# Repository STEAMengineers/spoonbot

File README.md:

# spoonbot
Spoonbot is a social energy indicator robot pcb based on a CH32v003J4M6 microcontroller, using a thumbwheel potentiometer to light some or all of the 5 leds.  It was designed for a smd soldering workshop we ran with MCQN at DoES Livepool.

This repo contains the code for the microcontroller and a kicad version of the pcb design. Because we used JLC colour silkscreen for our badges the hardware folder is an export from EasyEDA. It is highly recommended that you run DRC on the pcb before exporting for production.

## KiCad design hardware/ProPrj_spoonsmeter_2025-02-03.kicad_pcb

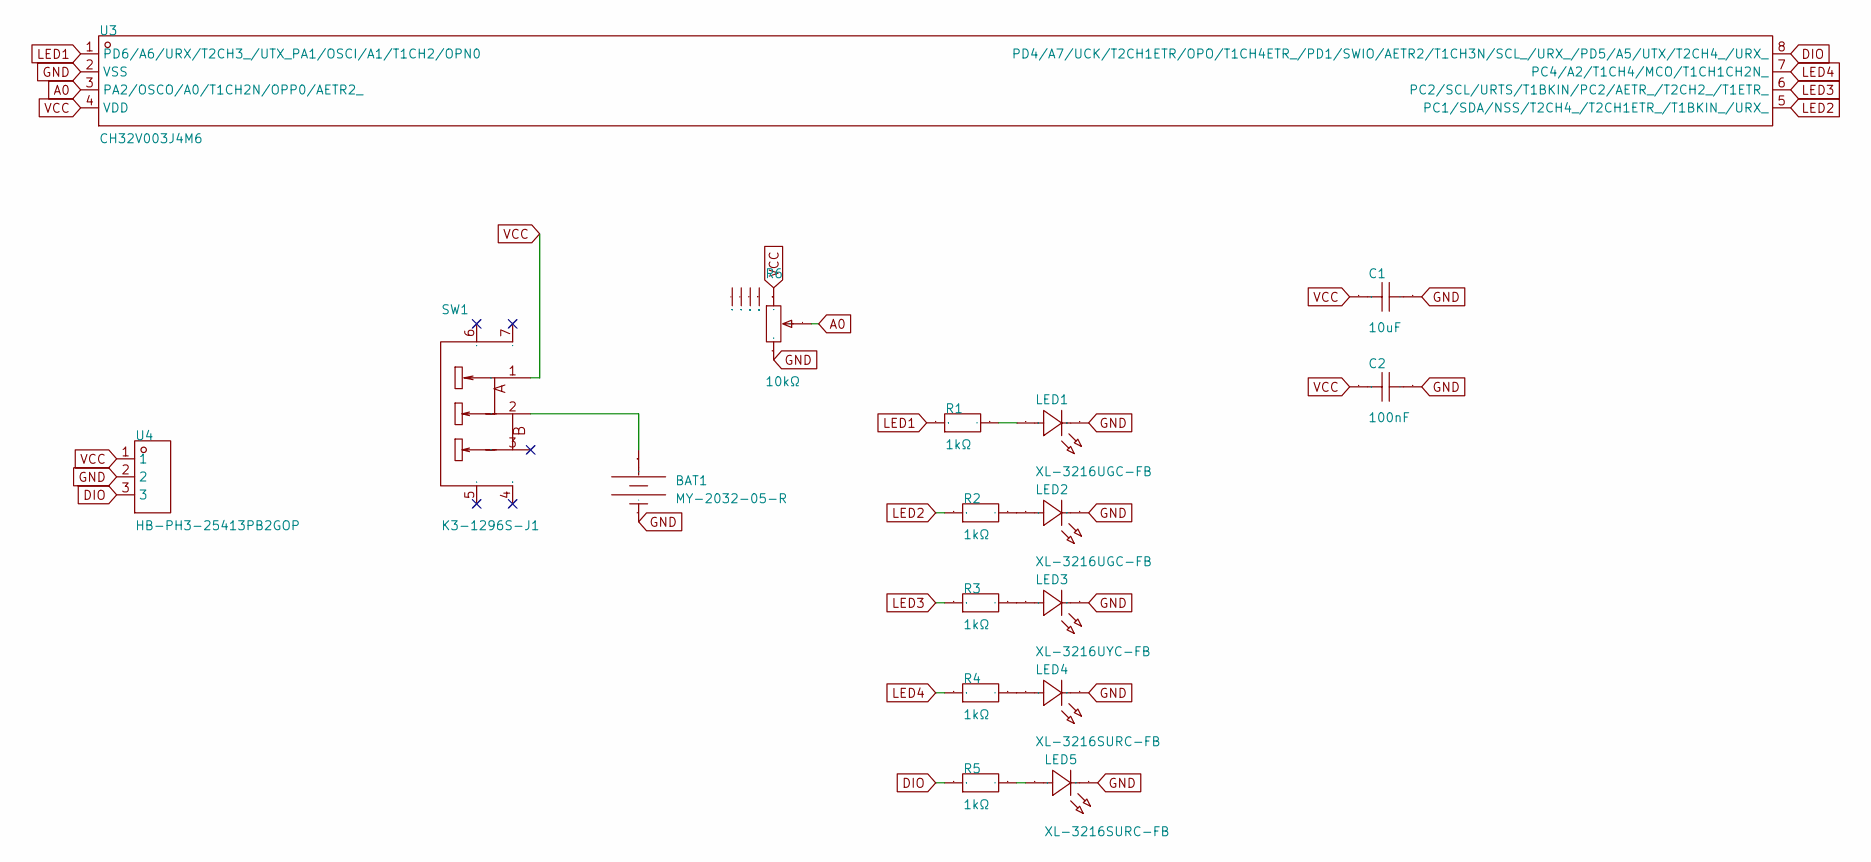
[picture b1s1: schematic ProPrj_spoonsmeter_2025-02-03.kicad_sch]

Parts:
BAT1: MY-2032-05-R; BAT-SMD_MY-2032-05-R; Manufacturer Part MY-2032-05-R; LCSC Part Name 电池扣 适用电池:CR2032
C1: 10uF; C0805; Manufacturer Part C0805X106K010T; LCSC Part Name 10uF ±10% 10V
C2: 100nF; C0805; Manufacturer Part C0805X104K251T; LCSC Part Name 100nF ±10% 250V
LED1, LED2: XL-3216UGC-FB; LED1206-RD_RED_LTST-C230CKT; Manufacturer Part XL-3216UGC-FB; LCSC Part Name XL-3216UGC-FB
LED3: XL-3216UYC-FB; LED1206-RD_RED_LTST-C230CKT; Manufacturer Part XL-3216UYC-FB; LCSC Part Name XL-3216UYC-FB
LED4, LED5: XL-3216SURC-FB; LED1206-RD_RED_LTST-C230CKT; Manufacturer Part XL-3216SURC-FB; LCSC Part Name XL-3216SURC-FB
R1, R2, R3, R4, R5: 1kΩ; R0805; Manufacturer Part SCR0805J1K; LCSC Part Name 厚膜电阻 1kΩ ±5% 125mW
R6: 10kΩ; RES-SMD_RK10J11R0A0H; Manufacturer Part RK10J11R0A0H; LCSC Part Name 10kΩ ±30%
SW1: K3-1296S-J1; SW-SMD_K3-1296S-J1; Manufacturer Part K3-1296S-J1; LCSC Part Name 柄长2.3mm卧贴双档 滑动开关
U3: CH32V003J4M6; SOP-8_L4.9-W3.8-P1.27-LS6.0-BL; Manufacturer Part CH32V003J4M6; LCSC Part Name CH32V003J4M6
U4: HB-PH3-25413PB2GOP; HDR-TH_3P-P2.54-V-M; Manufacturer Part HB-PH3-25413PB2GOP; LCSC Part Name 间距:2.54mm 1x3P 直插 方针

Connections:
$1N1644: BAT1.1 (+), SW1.2
$1N2487: LED3.2 (A), R3.2
$1N2528: LED2.2 (A), R2.2
$1N2533: LED4.2 (A), R4.2
$1N2535: LED1.2 (A), R1.2
$1N2553: LED5.2 (A), R5.2
A0: R6.2, U3.3 (PA2/OSCO/A0/T1CH2N/OPP0/AETR2_)
DIO: R5.1, U3.8 (PD4/A7/UCK/T2CH1ETR/OPO/T1CH4ETR_/PD1/S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), U4.3
GND: BAT1.2 (-), C1.2, C2.2, LED1.1 (K), LED2.1 (K), LED3.1 (K), LED4.1 (K), LED5.1 (K), R6.3, U3.2 (VSS), U4.2
LED1: R1.1, U3.1 (PD6/A6/URX/T2CH3_/UTX_PA1/OSCI/A1/T1CH2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)
LED2: R2.1, U3.5 (PC1/SDA/NSS/T2CH4_/T2CH1ETR_/T1BKIN_/UR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)
LED3: R3.1, U3.6 (PC2/SCL/URTS/T1BKIN/PC2/AETR_/T2CH2_/T1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)
LED4: R4.1, U3.7 (PC4/A2/T1CH4/MCO/T1CH1CH2N_)
VCC: C1.1, C2.1, R6.1, SW1.1, U3.4 (VDD), U4.1

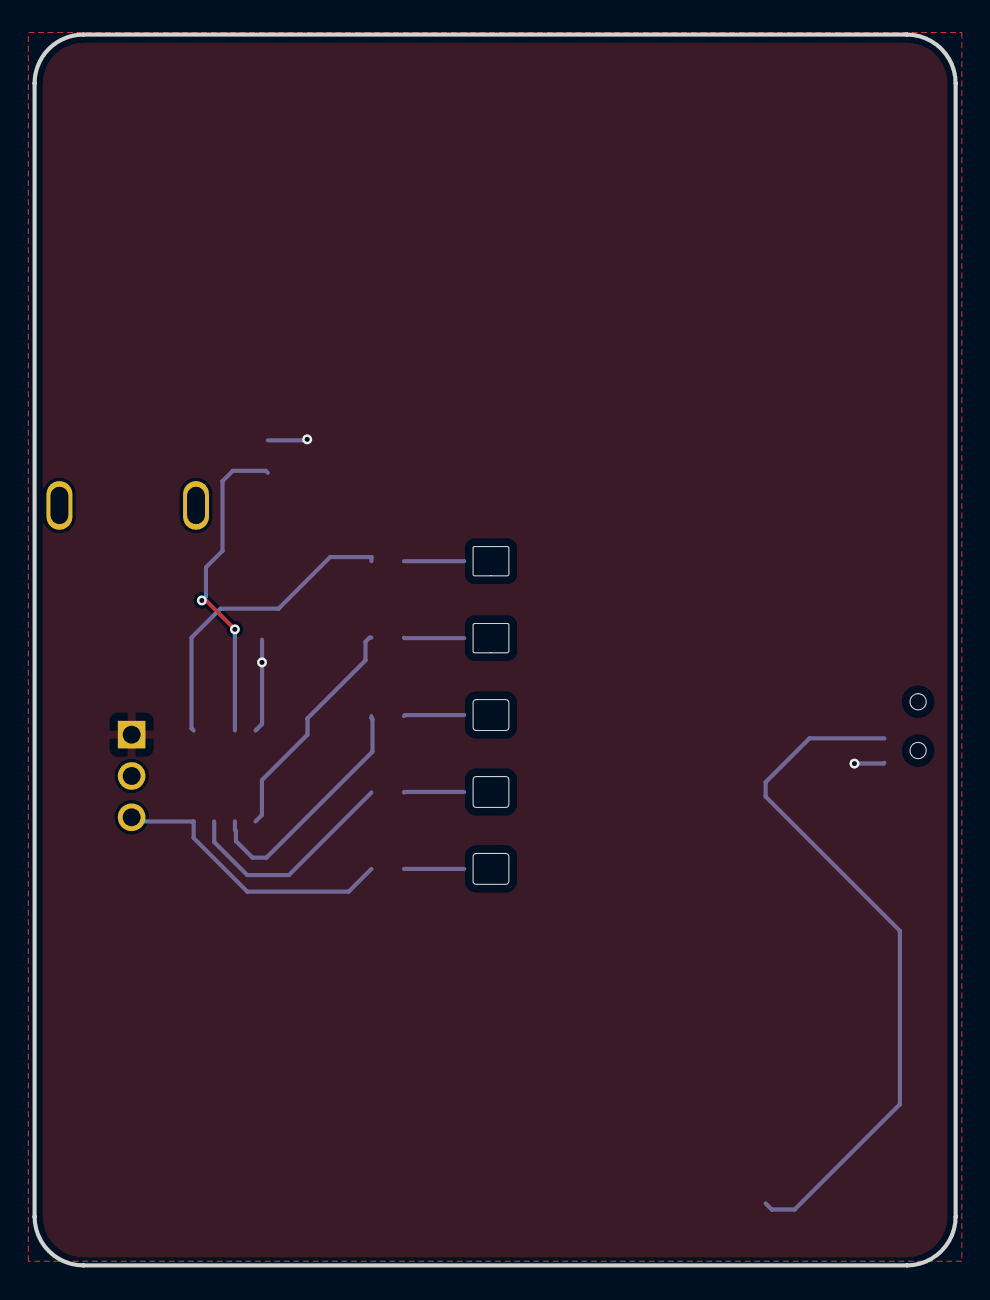
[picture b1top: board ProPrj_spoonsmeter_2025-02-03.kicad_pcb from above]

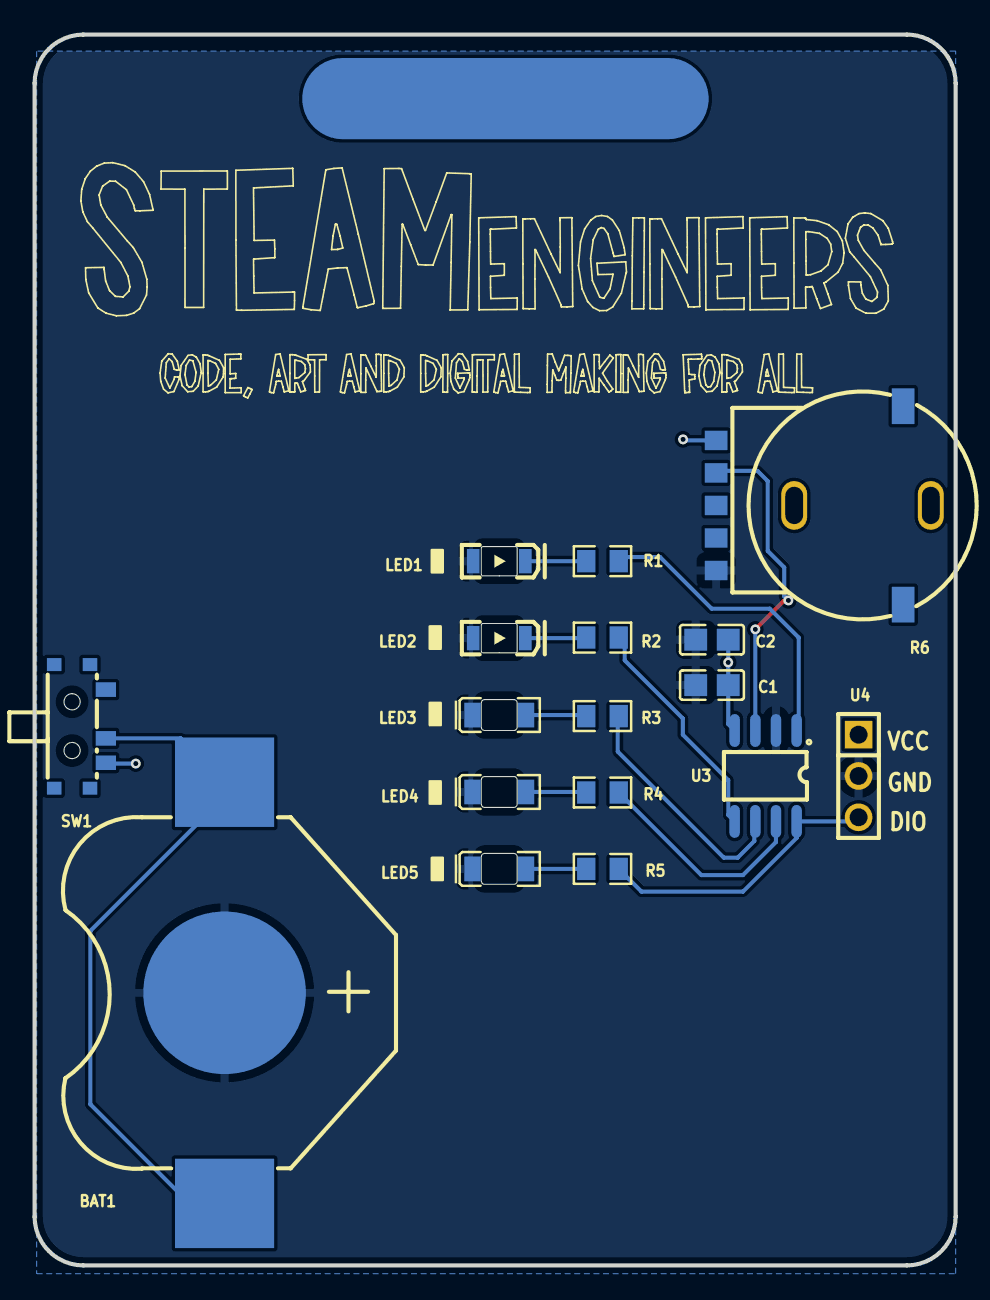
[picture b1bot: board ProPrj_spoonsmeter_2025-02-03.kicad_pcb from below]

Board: 2 copper layers, 56.6 x 75.7 mm, 17 parts (17 on the bottom side), 14 nets.

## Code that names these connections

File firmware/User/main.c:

/********************************** (C) COPYRIGHT *******************************
 * File Name          : main.c
 * Author             : WCH
 * Version            : V1.0.0
 * Date               : 2023/12/25
 * Description        : Main program body.
 *********************************************************************************
 * Copyright (c) 2021 Nanjing Qinheng Microelectronics Co., Ltd.
 * Attention: This software (modified or not) and binary are used for 
 * microcontroller manufactured by Nanjing Qinheng Microelectronics.
 *******************************************************************************/

/*
 *@Note
 *Multiprocessor communication mode routine:
 *Master:USART1_Tx(PD5)\USART1_Rx(PD6).
 *This routine demonstrates that USART1 receives the data sent by CH341 and inverts
 *it and sends it (baud rate 115200).
 *
 *Hardware connection:PD5 -- Rx
 *                     PD6 -- Tx
 *
 */

#include "debug.h"


/* Global define */


/* Global Variable */
vu8 val;

/*********************************************************************
 * @fn      init_gpio
 *
 * @brief   Initializes PC1,2 & 4 and PA1.
 *
 * @return  none
 */
void init_gpio(void)
{
    ADC_InitTypeDef ADC_InitStructure = {0};
    GPIO_InitTypeDef  GPIO_InitStructure = {0};

    RCC_APB2PeriphClockCmd(RCC_APB2Periph_GPIOC | RCC_APB2Periph_GPIOA | RCC_APB2Periph_GPIOD, ENABLE);

    /* Port C1=led2 2=led3 4=led4 */
    GPIO_InitStructure.GPIO_Pin = GPIO_Pin_1 | GPIO_Pin_2 | GPIO_Pin_4;
    GPIO_InitStructure.GPIO_Speed = GPIO_Speed_30MHz;
    GPIO_InitStructure.GPIO_Mode = GPIO_Mode_Out_PP;
    GPIO_Init(GPIOC, &GPIO_InitStructure);

    /* Port D6=led1 D4=led5*/
    GPIO_InitStructure.GPIO_Pin = GPIO_Pin_6 | GPIO_Pin_4;
    GPIO_InitStructure.GPIO_Speed = GPIO_Speed_30MHz;
    GPIO_InitStructure.GPIO_Mode = GPIO_Mode_Out_PP;
    GPIO_Init(GPIOD, &GPIO_InitStructure);

    /* Port A0*/

     RCC_APB2PeriphClockCmd(RCC_APB2Periph_GPIOA, ENABLE);
     RCC_APB2PeriphClockCmd(RCC_APB2Periph_ADC1, ENABLE);
     RCC_ADCCLKConfig(RCC_PCLK2_Div8);

     GPIO_InitStructure.GPIO_Pin = GPIO_Pin_2;
     GPIO_InitStructure.GPIO_Mode = GPIO_Mode_AIN;
     GPIO_Init(GPIOA, &GPIO_InitStructure);
     
     ADC_DeInit(ADC1);
     ADC_InitStructure.ADC_Mode = ADC_Mode_Independent;
     ADC_InitStructure.ADC_ScanConvMode = DISABLE;
     ADC_InitStructure.ADC_ContinuousConvMode = ENABLE; 
     ADC_InitStructure.ADC_ExternalTrigConv = ADC_ExternalTrigConv_None; 
     ADC_InitStructure.ADC_DataAlign = ADC_DataAlign_Right;
     ADC_InitStructure.ADC_NbrOfChannel = 1; 
     ADC_Init(ADC1, &ADC_InitStructure);

     ADC_RegularChannelConfig(ADC1, ADC_Channel_0, 1, ADC_SampleTime_241Cycles);

     ADC_Cmd(ADC1, ENABLE);
     ADC_ResetCalibration(ADC1);
     while(ADC_GetResetCalibrationStatus(ADC1));
     ADC_StartCalibration(ADC1);
     while(ADC_GetCalibrationStatus(ADC1));

     ADC_SoftwareStartConvCmd(ADC1, ENABLE);


}

/*********************************************************************
 * @fn      blink
 *
 * @brief   toggle leds
 *
 * @return  none
 */
void blink_gpio(void)
{
    GPIO_WriteBit(GPIOC, GPIO_Pin_1, (GPIO_ReadOutputDataBit(GPIOC, GPIO_Pin_1) == Bit_SET) ? Bit_RESET : Bit_SET );
    Delay_Ms(50);

    GPIO_WriteBit(GPIOC, GPIO_Pin_2, (GPIO_ReadOutputDataBit(GPIOC, GPIO_Pin_2) == Bit_SET) ? Bit_RESET : Bit_SET );
    Delay_Ms(50);

    GPIO_WriteBit(GPIOC, GPIO_Pin_4, (GPIO_ReadOutputDataBit(GPIOC, GPIO_Pin_4) == Bit_SET) ? Bit_RESET : Bit_SET );
    Delay_Ms(50);

    GPIO_WriteBit(GPIOD, GPIO_Pin_6, (GPIO_ReadOutputDataBit(GPIOD, GPIO_Pin_6) == Bit_SET) ? Bit_RESET : Bit_SET );
    Delay_Ms(50);

    GPIO_WriteBit(GPIOD, GPIO_Pin_4, (GPIO_ReadOutputDataBit(GPIOD, GPIO_Pin_4) == Bit_SET) ? Bit_RESET : Bit_SET );
    Delay_Ms(50);

}
void Get_ADC_Val(void)
{
    uint16_t adcValue = ADC_GetConversionValue(ADC1);

    if(adcValue < 10)    
    {
        GPIO_WriteBit(GPIOD, GPIO_Pin_4, Bit_RESET ); //led5        
        GPIO_WriteBit(GPIOC, GPIO_Pin_4, Bit_RESET ); //led4
        GPIO_WriteBit(GPIOC, GPIO_Pin_2, Bit_RESET ); //led3
        GPIO_WriteBit(GPIOC, GPIO_Pin_1, Bit_RESET ); //led2
        GPIO_WriteBit(GPIOD, GPIO_Pin_6, Bit_RESET ); //led1       
    } else if(adcValue < 200) {
        GPIO_WriteBit(GPIOD, GPIO_Pin_4, Bit_SET ); //led5
        GPIO_WriteBit(GPIOC, GPIO_Pin_4, Bit_RESET ); //led4
        GPIO_WriteBit(GPIOC, GPIO_Pin_2, Bit_RESET ); //led3
        GPIO_WriteBit(GPIOC, GPIO_Pin_1, Bit_RESET ); //led2
        GPIO_WriteBit(GPIOD, GPIO_Pin_6, Bit_RESET ); //led1 
    } else if(adcValue < 400) {
        GPIO_WriteBit(GPIOD, GPIO_Pin_4, Bit_SET ); //led5
        GPIO_WriteBit(GPIOC, GPIO_Pin_4, Bit_SET ); //led4
        GPIO_WriteBit(GPIOC, GPIO_Pin_2, Bit_RESET ); //led3
        GPIO_WriteBit(GPIOC, GPIO_Pin_1, Bit_RESET ); //led2
        GPIO_WriteBit(GPIOD, GPIO_Pin_6, Bit_RESET ); //led1
    }  else if(adcValue < 600) {
        GPIO_WriteBit(GPIOD, GPIO_Pin_4, Bit_SET ); //led5
        GPIO_WriteBit(GPIOC, GPIO_Pin_4, Bit_SET ); //led4
        GPIO_WriteBit(GPIOC, GPIO_Pin_2, Bit_SET ); //led3
        GPIO_WriteBit(GPIOC, GPIO_Pin_1, Bit_RESET ); //led2
        GPIO_WriteBit(GPIOD, GPIO_Pin_6, Bit_RESET ); //led1 
    }  else if(adcValue < 800) {
        GPIO_WriteBit(GPIOD, GPIO_Pin_4, Bit_SET ); //led5
        GPIO_WriteBit(GPIOC, GPIO_Pin_4, Bit_SET ); //led4
        GPIO_WriteBit(GPIOC, GPIO_Pin_2, Bit_SET ); //led3
        GPIO_WriteBit(GPIOC, GPIO_Pin_1, Bit_SET ); //led2
        GPIO_WriteBit(GPIOD, GPIO_Pin_6, Bit_RESET ); //led1 
    } else {
        GPIO_WriteBit(GPIOD, GPIO_Pin_4, Bit_SET ); //led5
        GPIO_WriteBit(GPIOC, GPIO_Pin_4, Bit_SET ); //led4
        GPIO_WriteBit(GPIOC, GPIO_Pin_2, Bit_SET ); //led3
        GPIO_WriteBit(GPIOC, GPIO_Pin_1, Bit_SET ); //led2
        GPIO_WriteBit(GPIOD, GPIO_Pin_6, Bit_SET ); //led1  
    }
           
    // Delay_Ms(1000);
    
}


/*********************************************************************
 * @fn      main
 *
 * @brief   Main program.
 *
 * @return  none
 */
int main(void)
{
    NVIC_PriorityGroupConfig(NVIC_PriorityGroup_1);
    SystemCoreClockUpdate();
    Delay_Init();
  /*  USART_Printf_Init(115200);
    USARTx_CFG();
    printf("helllllo")
    Delay_Ms(3000); */
    init_gpio();
    blink_gpio();

    while(1) 
    {
    Get_ADC_Val();
    }
}

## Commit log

2025-02-03 Add moun river code to Firmware
2025-02-03 Add kicad files
2025-02-04 Update kicad pcb files
2025-02-10 Add licence
2025-02-11 Update README.md
    proofread
